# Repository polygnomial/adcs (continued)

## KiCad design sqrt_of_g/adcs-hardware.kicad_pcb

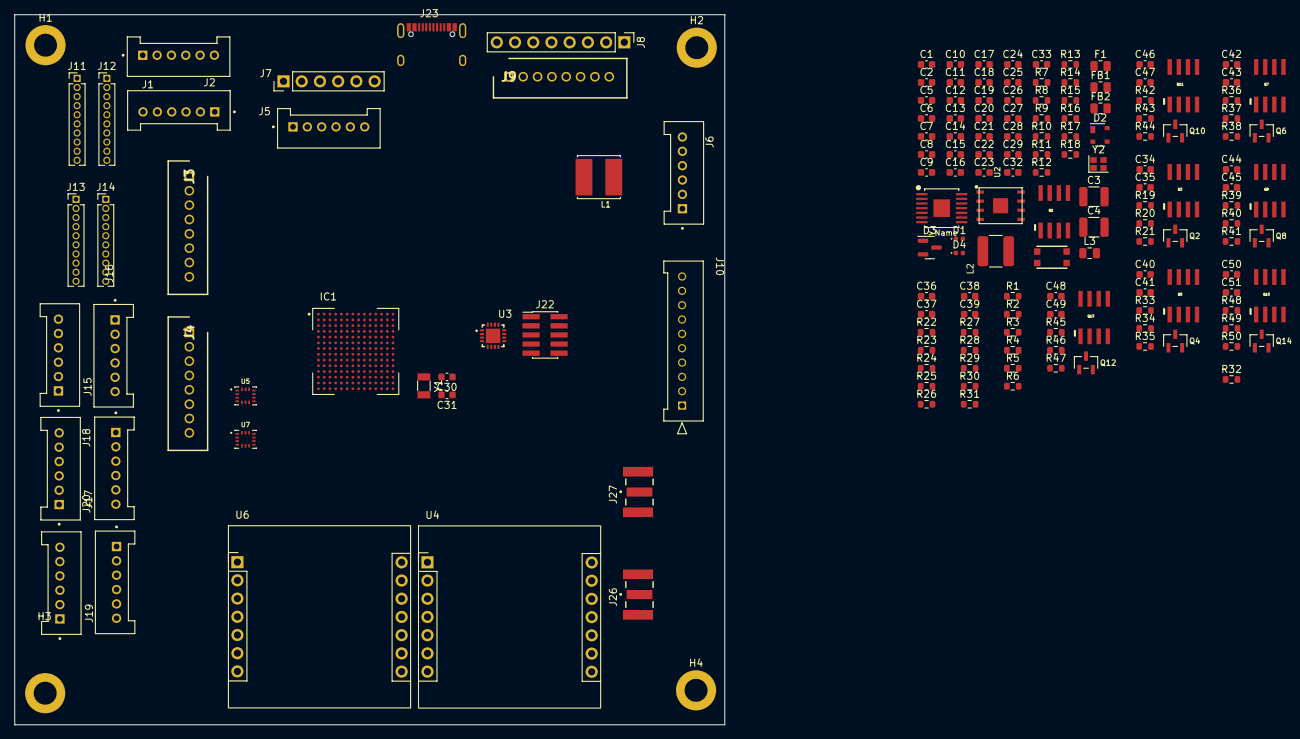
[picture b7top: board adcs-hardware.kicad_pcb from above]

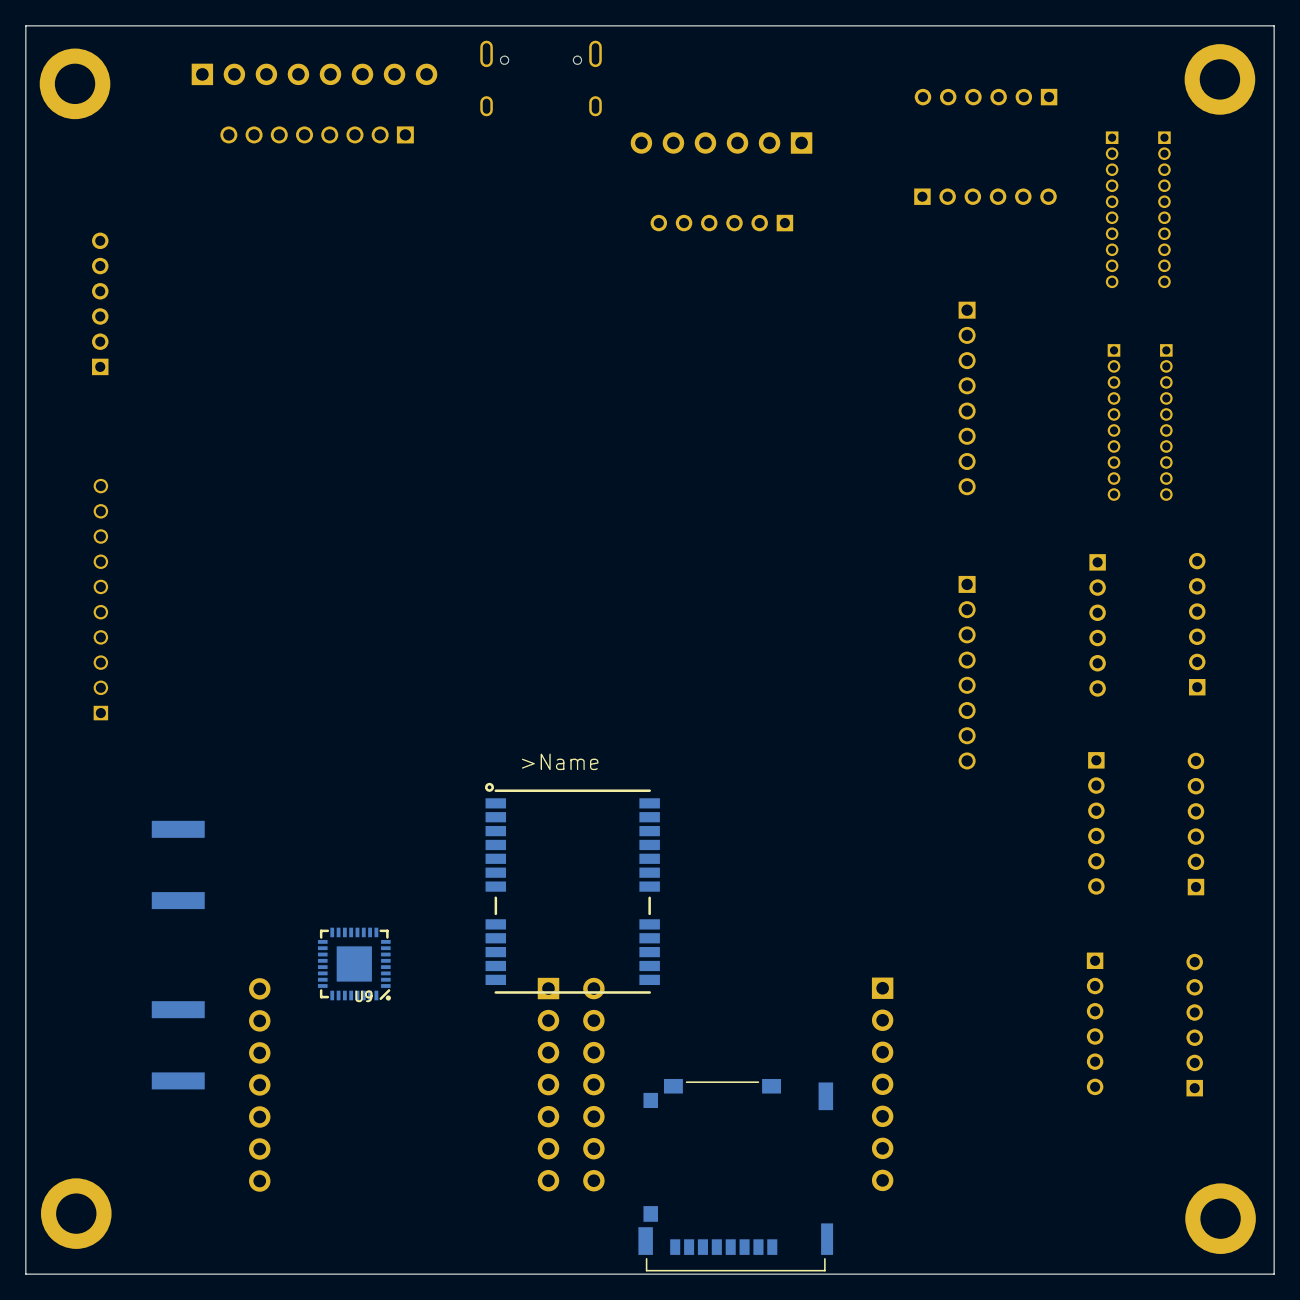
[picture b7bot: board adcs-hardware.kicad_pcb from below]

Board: 2 copper layers, 99.0 x 99.0 mm, 168 parts (3 on the bottom side), 189 nets, no tracks yet.

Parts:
C1, C2: 22uF; C_0603_1608Metric
C3, C4: 100uF; C_1210_3225Metric
C5, C9, C36, C37, C38, C39: 0.1uF; C_0603_1608Metric
C6, C7, C12, C16, C17, C23, C35, C41, C43, C45, C47, C49, C51: 4.7uF; C_0603_1608Metric
C8, C13, C15, C19, C20, C21, C22, C24, C25: 0.22uF; C_0603_1608Metric
C10: 3.3nF; C_0603_1608Metric
C11: 1uF; C_0603_1608Metric
C14, C27, C28, C29: 10uF; C_0603_1608Metric
C18, C34, C40, C42, C44, C46, C48, C50: 10nF; C_0603_1608Metric
C26: 2.2uF; C_0603_1608Metric
C30, C31, C32, C33: 10pF; C_0603_1608Metric
D1, D4: LED; LED_0402_1005Metric
D2: TVS Diode; SOT-143
D3: BAT54C; SOT-23
F1: Fuse; R_0805_2012Metric
FB1, FB2: FerriteBead; R_0805_2012Metric
H1, H2, H3, H4: MountingHole_Pad; MountingHole_3.2mm_M3_DIN965_Pad
IC1: MIMXRT1062DVJ6B; BGA196C80P14X14_1200X1200X152N
J1, J2, J5, J6, J15, J16, J17, J18, J19, J20: 353620650; MOLEX_35362-0650
J3, J4, J9: 353620850; SHDR8W50P0X200_1X8_1830X550X850P
J7: Conn_01x06; PinHeader_1x06_P2.54mm_Vertical
J8: Control Debug Header; PinHeader_1x08_P2.54mm_Vertical
J10: Thruster Connector; CON_353621050
J11, J12, J13, J14: Conn_01x10; PinHeader_1x10_P1.27mm_Vertical
J22: JTAG_SWD_10; PinHeader_2x05_P1.27mm_Vertical_SMD
J23: USB_C_pycubed; USB_C_Receptacle_XKB_U262-161N-4BVC11
J25: 503182-1852; MOLEX_503182-1852
J26, J27: SMA-J-P-H-ST-EM1; SAMTEC_SMA-J-P-H-ST-EM1
L1: 330uH; IND_SRN6045TA-331K
L2: 3.3uH; L_2141
L3: 4.7uH; C_0805_2012Metric
Q1, Q3, Q5, Q7, Q9, Q11, Q13, Q15: NDS8434
Q2, Q4, Q6, Q8, Q10, Q12, Q14: IRLML2803; SOT-23
R1, R2, R3, R4, R5, R6: 0; R_0603_1608Metric
R7: 73.2K; R_0603_1608Metric
R8, R17: 1k; R_0603_1608Metric
R9, R14: 100K; R_0603_1608Metric
R10: 22.1K; R_0603_1608Metric
R11, R12: 5.1k; R_0603_1608Metric
R13, R15, R18, R22, R23, R24, R25, R26, R27, R28, R29, R30, R31: 10k; R_0603_1608Metric
R16, R21, R35: 100k; R_0603_1608Metric
R19, R32, R33, R36, R39, R42, R45, R48: 10K; R_0603_1608Metric
R20, R34, R37, R40, R43, R46, R49: 4.7K; R_0603_1608Metric
R38, R41, R44, R47, R50: 3.3k; R_0603_1608Metric
SW1: KMR231NG LFS; BTN_KMR2_4.6X2.8
U1: TPS54226PWPR; PWP14_2P31X2P46-L
U2: MR25H40MDF; SON127P600X500X90-9N
U3: MKL02Z32VFG4; QFN50P300X300X65-17N
U4, U6: RM3100 Dev Board; RM3100
U5, U7: BMI270; XDCR_BMI270
U8: Orion B16; S1216_24PIN_PACKAGE
U9: EP2W+; QFN32-5X5MM
Y1: 32.768kHz; Crystal_SMD_3215-2Pin_3.2x1.5mm
Y2: 24.0mHz; Crystal_SMD_2016-4Pin_2.0x1.6mm

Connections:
3.3V: C9.1, D3.2, J25.4 (VDD), R13.2, R15.2, U2.8 (VDD)
+3V3: C1.2, C2.2, D1.2 (A), FB2.1, J5.1, J7.1, J15.4, J16.4, J17.4, J18.4, J19.4, J20.4, J22.1 (VTref), L2.2, Q7.1 (Source), Q7.2 (Source), Q7.3 (Source), Q9.1 (Source), Q9.2 (Source), Q9.3 (Source), Q11.1 (Source), Q11.2 (Source), Q11.3 (Source), Q13.1 (Source), Q13.2 (Source), Q13.3 (Source), Q15.1 (Source), Q15.2 (Source), Q15.3 (Source), R7.2, R9.2, R38.1, R41.1, R44.1, R47.1, R50.1, U1.1 (VO), U3.1 (VDD)
+5V: IC1.N6 (USB_OTG1_VBUS), IC1.P6 (USB_OTG2_VBUS), Q1.1 (Source), Q1.2 (Source), Q1.3 (Source)
+5VD: C6.2, D2.2 (K), F1.1, J5.6, J7.6, J23.A4 (VBUS), J23.A9 (VBUS)
/3V3_PD1: C48.1, C49.1, J2.1, J3.1, J3.5, Q13.5 (Drain), Q13.6 (Drain), Q13.7 (Drain), Q13.8 (Drain)
/3V3_PD2: C50.1, C51.1, J1.1, J4.1, J4.5, Q15.5 (Drain), Q15.6 (Drain), Q15.7 (Drain), Q15.8 (Drain)
/ADCS Power Enable/VBUS_IN: L1.2, Q5.1 (Source), Q5.2 (Source), Q5.3 (Source), R35.1
/Coil Power Enable/VBUS_OUT: C34.1, C35.1, J15.5, J16.5, J17.5, J18.5, J19.5, J20.5, Q3.5 (Drain), Q3.6 (Drain), Q3.7 (Drain), Q3.8 (Drain)
/EN_COILS: IC1.M14 (GPIO_AD_B0_00), R19.1, R20.1
/GPS/3V3_GPS: C46.1, C47.1, Q11.5 (Drain), Q11.6 (Drain), Q11.7 (Drain), Q11.8 (Drain), R32.2, U8.22 (V_BCKP), U8.23 (VCC)
/GPS/EN_GPS: IC1.E8 (GPIO_B0_02), R42.1, R43.1
/GPS/RF_IN: U8.11 (RF_IN), U9.4 (SUM_PORT)
/IMU1_and_MAG1/3V3_SENSORS: C36.1, C37.1, C42.1, C43.1, Q7.5 (Drain), Q7.6 (Drain), Q7.7 (Drain), Q7.8 (Drain), R24.2, R25.1, R26.1, U4.12 (DVDD), U4.13 (AVDD), U5.5 (VDDIO), U5.8 (VDD), U5.10 (OSCB)
/IMU1_and_MAG1/DRDY_MAG: IC1.C12 (GPIO_B1_06), U4.5 (DRDY)
/IMU1_and_MAG1/EN_SENSORS: IC1.E7 (GPIO_B0_01), R36.1, R37.1
/IMU2_and_MAG2/3V3_SENSORS: C38.1, C39.1, C44.1, C45.1, Q9.5 (Drain), Q9.6 (Drain), Q9.7 (Drain), Q9.8 (Drain), R29.2, R30.1, R31.1, U6.12 (DVDD), U6.13 (AVDD), U7.5 (VDDIO), U7.8 (VDD), U7.10 (OSCB)
/IMU2_and_MAG2/DRDY_MAG: IC1.D7 (GPIO_B0_00), U6.5 (DRDY)
/IMU2_and_MAG2/EN_SENSORS: IC1.A12 (GPIO_B1_08), R39.1, R40.1
/MCU/FLASH.CS: IC1.P5 (GPIO_SD_B1_11), U2.7 (~HOLD)
/MCU/FLASH.IO0: IC1.P3 (GPIO_SD_B1_08), U2.3 (~WP)
/MCU/FLASH.IO1: IC1.P4 (GPIO_SD_B1_10), U2.6 (SCK)
/MCU/FLASH.IO2: IC1.N4 (GPIO_SD_B1_09), U2.5 (SI)
/MCU/FLASH.IO3: IC1.L3 (GPIO_SD_B1_06), R15.1, U2.1 (~CS)
/MCU/FLASH.SCK: IC1.L4 (GPIO_SD_B1_07), U2.2 (SO)
/MCU/GPIO_AD_B0_01: IC1.H10 (GPIO_AD_B0_01), R5.1
/MCU/GPIO_AD_B0_03: IC1.G11 (GPIO_AD_B0_03), R6.1
/MCU/GPIO_AD_B0_12: IC1.K14 (GPIO_AD_B0_12), J3.3
/MCU/GPIO_AD_B0_13: IC1.L14 (GPIO_AD_B0_13), J3.4
/MCU/GPIO_AD_B0_14: IC1.H14 (GPIO_AD_B0_14), J3.7
/MCU/GPIO_AD_B0_15: IC1.L10 (GPIO_AD_B0_15), J3.8
/MCU/GPIO_AD_B1_00: IC1.J11 (GPIO_AD_B1_00), J2.3
/MCU/GPIO_AD_B1_01: IC1.K11 (GPIO_AD_B1_01), J2.4
/MCU/GPIO_AD_B1_04: IC1.L12 (GPIO_AD_B1_04), J2.5
/MCU/GPIO_AD_B1_05: IC1.K12 (GPIO_AD_B1_05), J2.6
/MCU/GPIO_AD_B1_06: IC1.J12 (GPIO_AD_B1_06), J4.3
/MCU/GPIO_AD_B1_07: IC1.K10 (GPIO_AD_B1_07), J4.4
/MCU/GPIO_AD_B1_08: IC1.H13 (GPIO_AD_B1_08), J4.7
/MCU/GPIO_AD_B1_09: IC1.M13 (GPIO_AD_B1_09), J4.8
/MCU/GPIO_AD_B1_10: IC1.L13 (GPIO_AD_B1_10), J1.3
/MCU/GPIO_AD_B1_11: IC1.J13 (GPIO_AD_B1_11), J1.4
/MCU/GPIO_AD_B1_12: IC1.H12 (GPIO_AD_B1_12), J1.5
/MCU/GPIO_AD_B1_13: IC1.H11 (GPIO_AD_B1_13), J1.6
/MCU/GPIO_AD_B1_14: IC1.G12 (GPIO_AD_B1_14), J14.5
/MCU/GPIO_AD_B1_15: IC1.J14 (GPIO_AD_B1_15), J14.6
/MCU/GPIO_B0_06: IC1.A8 (GPIO_B0_06), R48.1, R49.1
/MCU/GPIO_B0_07: IC1.A9 (GPIO_B0_07), R45.1, R46.1
/MCU/GPIO_B0_08: IC1.B9 (GPIO_B0_08), J13.1
/MCU/GPIO_B0_09: IC1.C9 (GPIO_B0_09), J13.2
/MCU/GPIO_B0_10: IC1.D9 (GPIO_B0_10), J13.3
/MCU/GPIO_B0_11: IC1.A10 (GPIO_B0_11), J13.4
/MCU/GPIO_B0_12: IC1.C10 (GPIO_B0_12), J13.5
/MCU/GPIO_B0_14: IC1.E10 (GPIO_B0_14), J13.6
/MCU/GPIO_B1_02: IC1.C11 (GPIO_B1_02), J12.1
/MCU/GPIO_B1_03: IC1.D11 (GPIO_B1_03), J12.2
/MCU/GPIO_B1_04: IC1.E12 (GPIO_B1_04), J12.3
/MCU/GPIO_B1_05: IC1.D12 (GPIO_B1_05), J12.4
/MCU/GPIO_B1_07: IC1.B12 (GPIO_B1_07), J12.5
/MCU/GPIO_B1_09: IC1.A13 (GPIO_B1_09), J12.6
/MCU/GPIO_B1_10: IC1.B13 (GPIO_B1_10), J11.1
/MCU/GPIO_B1_11: IC1.C13 (GPIO_B1_11), J11.2
/MCU/GPIO_B1_12: IC1.D13 (GPIO_B1_12), J11.3
/MCU/GPIO_B1_13: IC1.D14 (GPIO_B1_13), J11.4
/MCU/GPIO_B1_14: IC1.C14 (GPIO_B1_14), J11.5
/MCU/GPIO_B1_15: IC1.B14 (GPIO_B1_15), IC1.E11 (GPIO_B0_15), J11.6
/MCU/GPIO_EMC_00: IC1.D6 (GPIO_EMC_38), IC1.E3 (GPIO_EMC_00), J11.7
/MCU/GPIO_EMC_03: IC1.G4 (GPIO_EMC_03), J11.8
/MCU/GPIO_EMC_04: IC1.F2 (GPIO_EMC_04), J11.9
/MCU/GPIO_EMC_05: IC1.G5 (GPIO_EMC_05), R1.1
/MCU/GPIO_EMC_06: IC1.H5 (GPIO_EMC_06), R2.1
/MCU/GPIO_EMC_07: IC1.H4 (GPIO_EMC_07), J10.6
/MCU/GPIO_EMC_08: IC1.H3 (GPIO_EMC_08), J10.7
/MCU/GPIO_EMC_09: IC1.C2 (GPIO_EMC_09), J10.8
/MCU/GPIO_EMC_10: IC1.G1 (GPIO_EMC_10), J10.9
/MCU/GPIO_EMC_13: IC1.A6 (GPIO_EMC_13), J10.2
/MCU/GPIO_EMC_14: IC1.B6 (GPIO_EMC_14), J10.3
/MCU/GPIO_EMC_15: IC1.B1 (GPIO_EMC_15), J10.4
/MCU/GPIO_EMC_16: IC1.A5 (GPIO_EMC_16), J10.5
/MCU/GPIO_EMC_18: IC1.B2 (GPIO_EMC_18), J12.7
/MCU/GPIO_EMC_19: IC1.B4 (GPIO_EMC_19), J12.8
/MCU/GPIO_EMC_20: IC1.A3 (GPIO_EMC_20), J12.9
/MCU/GPIO_EMC_21: IC1.C1 (GPIO_EMC_21), J13.7
/MCU/GPIO_EMC_30: IC1.C6 (GPIO_EMC_30), J13.9
/MCU/GPIO_EMC_31: IC1.C5 (GPIO_EMC_31), J14.7
/MCU/GPIO_EMC_32: IC1.D5 (GPIO_EMC_32), J14.8
/MCU/GPIO_EMC_33: IC1.C4 (GPIO_EMC_33), J14.9
/MCU/GPIO_EMC_34: IC1.D4 (GPIO_EMC_34), R3.1
/MCU/GPIO_EMC_39: IC1.B7 (GPIO_EMC_39), R4.1
/MCU/GPIO_SD_B1_00: IC1.L5 (GPIO_SD_B1_00), J14.1
/MCU/GPIO_SD_B1_01: IC1.M5 (GPIO_SD_B1_01), J14.2
/MCU/GPIO_SD_B1_02: IC1.M3 (GPIO_SD_B1_02), J14.3
/MCU/GPIO_SD_B1_03: IC1.M4 (GPIO_SD_B1_03), J14.4
/MCU/JTAG.MUX.MOD: IC1.F13 (GPIO_AD_B0_08), U3.13 (PTB5)
/MCU/JTAG.MUX.TCK: IC1.F12 (GPIO_AD_B0_07), J22.4 (SWDCLK/TCK), U3.8 (PTB0)
/MCU/JTAG.MUX.TDI: IC1.F14 (GPIO_AD_B0_09), J22.8 (NC/TDI), U3.7 (PTA7)
/MCU/JTAG.MUX.TDO: IC1.G13 (GPIO_AD_B0_10), J22.6 (SWO/TDO), U3.6 (PTA6)
/MCU/JTAG.MUX.TMS: IC1.E14 (GPIO_AD_B0_06), J22.2 (SWDIO/TMS), U3.5 (PTA5)
/MCU/JTAG.MUX.TRSTB: IC1.G10 (GPIO_AD_B0_11), IC1.K3 (DCDC_PSWITCH), J22.10 (~RESET), R16.2, U3.3 (PTA3)
/MCU/ONOFF: IC1.M6 (ONOFF), J8.2, J9.2
/MCU/PMIC_STBY_REQ: IC1.L7 (PMIC_STBY_REQ), J8.4, J9.4, R18.2
/MCU/POR_B: IC1.M7 (POR_B), J8.5, J9.5, U3.9 (PTB1)
/MCU/SD.CLK: IC1.J3 (GPIO_SD_B0_01), J25.5 (CLK)
/MCU/SD.CMD: IC1.J4 (GPIO_SD_B0_00), J25.3 (CMD)
/MCU/SD.DAT0: IC1.J1 (GPIO_SD_B0_02), J25.7 (DAT0)
/MCU/SD.DAT1: IC1.K1 (GPIO_SD_B0_03), J25.8 (DAT1)
/MCU/SD.DAT2: IC1.H2 (GPIO_SD_B0_04), J25.1 (DATA2)
/MCU/SD.DAT3: IC1.J2 (GPIO_SD_B0_05), J25.2 (CD/DAT3), R13.1
/MCU/USB1_CC1: J23.A5 (CC1), R11.2
/MCU/USB1_CC2: J23.B5 (CC2), R12.2
/MCU/USB1_D+: D2.4 (K), IC1.L8 (USB_OTG1_DP), J23.A6 (D+), J23.B6 (D+)
/MCU/USB1_D-: D2.3 (K), IC1.M8 (USB_OTG1_DN), J23.A7 (D-), J23.B7 (D-)
/MCU/WAKEUP: IC1.L6 (WAKEUP), J8.3, J9.3
/RX_FROM_GPS: IC1.B11 (GPIO_B1_01), U8.20 (TXD)
/RX_FROM_PYCUBED: IC1.L11 (GPIO_AD_B1_02), J8.6, J9.6
/SCL2: IC1.C8 (GPIO_B0_04), J15.1, J18.1, R25.2, U4.1 (SCK/SCL), U5.13 (SCX)
/SCL4: IC1.H1 (GPIO_EMC_12), J16.1, J17.1, J19.1, J20.1, R30.2, U6.1 (SCK/SCL), U7.13 (SCX)
/SDA2: IC1.B8 (GPIO_B0_05), J15.2, J18.2, R26.2, U4.3 (SI/SDA), U5.14 (SDX)
/SDA4: IC1.G3 (GPIO_EMC_11), J16.2, J17.2, J19.2, J20.2, R31.2, U6.3 (SI/SDA), U7.14 (SDX)
/TX_TO_GPS: IC1.A11 (GPIO_B1_00), U8.21 (RXD)
/TX_TO_PYCUBED: IC1.M12 (GPIO_AD_B1_03), J8.7, J9.7
/VBATT: C3.1, C4.1, C40.1, C41.1, J5.5, J7.5, Q3.1 (Source), Q3.2 (Source), Q3.3 (Source), Q5.5 (Drain), Q5.6 (Drain), Q5.7 (Drain), Q5.8 (Drain), R21.1, U1.13 (VIN), U1.14 (VCC)
/VBATT_IN: J6.1, J6.3, J6.5, L1.1
GND: C1.1, C2.1, C3.2, C4.2, C7.2, C8.2, C9.2, C10.2, C11.2, C12.2, C13.2, C14.2, C15.2, C16.2, C17.2, C18.2, C19.2, C20.2, C21.2, C22.2, C23.2, C24.2, C25.2, C26.2, C27.2, C28.2, C29.2, C30.2, C31.2, C32.2, C33.2, C36.2, C37.2, C38.2, C39.2, D4.1 (K), H1.1, H2.1, H3.1, H4.1, IC1.A1 (VSS_1), IC1.A14 (VSS_2), IC1.B5 (VSS_3), IC1.B10 (VSS_4), IC1.E2 (VSS_5), IC1.E13 (VSS_6), IC1.G7 (VSS_7), IC1.G8 (VSS_8), IC1.G14 (GPIO_AD_B0_05), IC1.H7 (VSS_9), IC1.H8 (VSS_10), IC1.J7 (VSS_11), IC1.J8 (VSS_12), IC1.K2 (VSS_13), IC1.K6 (TEST_MODE), IC1.K9 (NGND_KEL0), IC1.K13 (VSS_14), IC1.L9 (VSS_15), IC1.N1 (DCDC_GND_1), IC1.N2 (DCDC_GND_2), IC1.N5 (VSS_16), IC1.N8 (VSS_17), IC1.P1 (VSS_18), IC1.P14 (VSS_19), J1.2, J2.2, J3.2, J3.6, J4.2, J4.6, J5.2, J5.4, J6.2, J6.4, J6.6, J7.2, J7.4, J8.1, J9.1, J10.1, J10.10, J11.10, J12.10, J13.10, J14.10, J15.3, J16.3, J17.3, J18.3, J19.3, J20.3, J22.3 (GND), J22.5 (GND), J22.9 (GNDDetect), J25.6 (VSS), J25.P1 (SHIELD), J25.P2 (SHIELD), J25.P3 (SHIELD), J25.P4 (SHIELD), J25.P5 (SHIELD), J26.2_1, J27.2_1, Q1.4 (Gate), Q2.2 (S), Q4.2 (S), Q6.2 (S), Q8.2 (S), Q10.2 (S), Q12.2 (S), Q14.2 (S), R10.1, R16.1, R18.1, R19.2, R22.1, R23.1, R27.1, R28.1, R33.1, R33.2, R34.1, R36.2, R39.2, R42.2, R45.2, R48.2, SW1.B (S), SW1.B' (S1), U1.5 (GND), U1.8 (PGND1), U1.9 (PGND2), U1.15 (EPAD), U2.4 (VSS), U2.9 (EP), U3.2 (VSS), U3.17 (EPAD), U4.7 (AVSS), U4.14 (DVSS), U5.1 (SDO), U5.6 (GNDIO), U5.7 (GND), U6.7 (AVSS), U6.14 (DVSS), U7.1 (SDO), U7.6 (GNDIO), U7.7 (GND), U8.10 (GND@10), U8.12 (GND@12), U8.13 (GND@13), U8.24 (GND@24), U9.1 (GND), U9.2 (GND), U9.3 (GND), U9.5 (GND), U9.6 (GND), U9.7 (GND), U9.8 (GND), U9.9 (GND), U9.10 (GND), U9.11 (GND), U9.12 (GND), U9.13 (GND), U9.14 (GND), U9.16 (GND), U9.17 (GND), U9.18 (GND), U9.19 (GND), U9.20 (GND), U9.21 (GND), U9.22 (GND), U9.23 (GND), U9.24 (GND), U9.25 (GND), U9.27 (GND), U9.28 (GND), U9.29 (GND), U9.30 (GND), U9.31 (GND), U9.32 (GND), U9.EP (GND)
GNDREF: C6.1, D2.1 (A), J5.3, J7.3, J23.A1 (GND), J23.A12 (GND), J23.S1 (SHIELD), R11.1, R12.1
unnamed: C34.2, C35.2
unnamed: C40.2, C41.2
unnamed: C42.2, C43.2
unnamed: C44.2, C45.2
unnamed: C46.2, C47.2
unnamed: C48.2, C49.2
unnamed: C50.2, C51.2
unnamed: D1.1 (K), R8.2
unnamed: D4.2 (A), R17.2
unnamed: F1.2, FB1.1
unnamed: FB1.2, Q1.5 (Drain), Q1.6 (Drain), Q1.7 (Drain), Q1.8 (Drain)
unnamed: C17.1, C24.1, C28.1, FB2.2, IC1.L1 (DCDC_IN_1), IC1.L2 (DCDC_IN_2)
unnamed: IC1.M1 (DCDC_LP_1), IC1.M2 (DCDC_LP_2), L3.2
unnamed: C18.1, C23.1, C25.1, C29.1, IC1.F6 (VDD_SOC_IN_1), IC1.F7 (VDD_SOC_IN_2), IC1.F8 (VDD_SOC_IN_3), IC1.F9 (VDD_SOC_IN_4), IC1.G6 (VDD_SOC_IN_5), IC1.G9 (VDD_SOC_IN_6), IC1.H6 (VDD_SOC_IN_7), IC1.H9 (VDD_SOC_IN_8), IC1.J5 (DCDC_SENSE), IC1.J9 (VDD_SOC_IN_9), L3.1
unnamed: C15.1, C16.1, C21.1, C22.1, C26.1, C27.1, IC1.E6 (NVCC_EMC_1), IC1.E9 (NVCC_GPIO_1), IC1.F4 (GPIO_EMC_02), IC1.F5 (NVCC_EMC_2), IC1.F10 (NVCC_GPIO_2), IC1.J6 (NVCC_SD0), IC1.J10 (NVCC_GPIO_3), IC1.K4 (DCDC__IN_Q), IC1.K5 (NVCC_SD1), IC1.N14 (VDDA_ADC_3P3), IC1.P12 (VDD_HIGH_IN)
unnamed: IC1.F11 (GPIO_AD_B0_04), U3.4 (PTA4)
unnamed: IC1.D8 (GPIO_B0_03), R17.1
unnamed: IC1.D10 (GPIO_B0_13), U3.12 (PTB4)
unnamed: IC1.F3 (GPIO_EMC_01), U3.15 (PTA1)
unnamed: C12.1, C13.1, IC1.P10 (NVCC_PLL)
unnamed: IC1.K7 (PMIC_ON_REQ), R9.1, U1.7 (EN)
unnamed: C33.1, IC1.N9 (RTC_XTALI), Y2.1
unnamed: C32.1, IC1.P9 (RTC_XTALO), Y2.2
unnamed: C7.1, C8.1, IC1.P8 (VDD_HIGH_CAP)
unnamed: C19.1, IC1.M10 (VDD_SNVS_CAP)
unnamed: D3.3, IC1.M9 (VDD_SNVS_IN)
unnamed: C14.1, C20.1, D3.1, IC1.K8 (VDD_USB_CAP)
unnamed: C31.1, IC1.P11 (XTALI), Y1.1
unnamed: C30.1, IC1.N11 (XTALO), Y1.2
unnamed: J15.6, R1.2
unnamed: J16.6, R2.2
unnamed: J17.6, R3.2
unnamed: J18.6, R4.2
unnamed: J19.6, R5.2
unnamed: J20.6, R6.2
unnamed: Q2.3 (D), Q3.4 (Gate), R21.2
unnamed: Q2.1 (G), R20.2
unnamed: Q4.3 (D), Q5.4 (Gate), R35.2
unnamed: Q4.1 (G), R34.2
unnamed: Q6.3 (D), Q7.4 (Gate), R38.2
unnamed: Q6.1 (G), R37.2
unnamed: Q8.3 (D), Q9.4 (Gate), R41.2
unnamed: Q8.1 (G), R40.2
unnamed: Q10.3 (D), Q11.4 (Gate), R44.2
unnamed: Q10.1 (G), R43.2
unnamed: Q12.3 (D), Q13.4 (Gate), R47.2
unnamed: Q12.1 (G), R46.2
unnamed: Q14.3 (D), Q15.4 (Gate), R50.2
unnamed: Q14.1 (G), R49.2
unnamed: SW1.A, SW1.A' (P1), U3.10 (PTB2)
unnamed: R14.1, U1.6 (PG)
unnamed: C10.1, U1.4 (SS)
unnamed: C5.1, L2.1, U1.10 (SW1), U1.11 (SW2)
unnamed: C5.2, U1.12 (VBST)
unnamed: R7.1, R10.2, U1.2 (VFB)
unnamed: C11.1, R14.2, U1.3 (VREG5)
unnamed: R8.1, U3.11 (PTB3)
unnamed: R24.1, U4.10 (I2CEN)
unnamed: R22.2, U4.2 (SO/ADDR1)
unnamed: R23.2, U4.4 (SSN/ADDR0)
unnamed: R29.1, U6.10 (I2CEN)
unnamed: R27.2, U6.2 (SO/ADDR1)
unnamed: R28.2, U6.4 (SSN/ADDR0)
unnamed: R32.1, U8.8 (RSTN)
unnamed: J27.1, U9.15 (PORT1)
unnamed: J26.1, U9.26 (PORT2)

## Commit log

2023-10-06 add gitignore
2023-10-06 add rough schematic
2023-10-10 schematic update
2023-10-10 add datasheet for teensy
2023-10-10 update schematic
2023-10-19 organize
2023-10-20 ready for review
2023-10-20 add datasheets
2023-10-20 beginning light sensing calcs
2023-10-20 add gnd pins
2023-10-20 pete feedback
2023-10-21 rename datasheets
2023-10-21 save
2023-10-25 add pyramidal breakout board
2023-10-25 move mainboard to subdirectory
2023-10-25 add math and decals
2023-10-26 ordered sfh2430 breakout rev 0.1
2023-10-30 more schematic work... I was supposed to finish this a long time ago
2023-10-30 add inertia calcs
2023-10-30 clean up msft gitignore
2023-10-30 add some symbols!
2023-11-01 ready for 2nd round of reviews
2023-11-01 add notes
2023-11-07 add mainboard footprints
2023-11-07 add footprints to adcs lib
2023-11-07 add models
2023-11-07 update ibom for photodiode breakout
2023-11-07 add C++ gitignore
2023-11-07 update board
2023-11-07 update pin map
2023-11-07 we have some software!
2023-11-07 move code up a folder
2023-11-07 fix RM3100 read bug and remove debug printing
2023-11-23 add pyramid stl
2023-11-24 sfh2400 v2 (flex PCB)
2023-11-25 add rusty flight target
2024-01-01 update libraries
2024-01-01 add kibot workflow
2024-01-01 rename kibot run
2024-01-01 oopsies
2024-01-01 update gps schematic
2024-01-01 update kibot version
2024-01-01 update main board
2024-01-01 remove prod folder
2024-01-01 add gps code
2024-01-01 add teensy 4.1 pinout
2024-01-01 add 3d models
2024-01-01 add rad testing reports for rm3100
2024-01-01 update pin map, add RT1176 pin map
2024-01-01 add rt1170 datasheet and mag sensor layout guidelines
2024-01-01 add note to tim review
2024-01-01 add FDSOI rad ref, mag sensor calibration references
2024-01-01 semi-working rust code
2024-01-01 add photodiode pics to the subdir
2024-01-01 try new kibot setup
2024-01-01 update run
2024-01-08 rust driver for RM3100, re-organize
2024-01-08 update gitignore
2024-01-08 don't ground enable pin
2024-01-08 migrate cpp code
2024-01-16 ffc/fpc pyramid
2024-01-16 add datasheet
2024-01-17 add submodules
2024-01-17 small
2024-01-17 add deps
2024-01-17 restore from backup
2024-01-17 bump libgeomag
2024-01-17 add triad
2024-01-17 optimize deps
2024-01-17 cargo fix
2024-01-18 switch to quaternion
2024-01-18 update libs
2024-02-02 fix photodiode pair
2024-02-02 add lots of datasheets
2024-02-02 update coil control
2024-02-02 add parts to library
2024-02-02 cpu board in progress
2024-02-05 b2b done, erc no errors
2024-02-05 work on sun pyramid
2024-02-05 update symbol library
2024-02-06 fix most footprints
2024-02-06 JLC parts list complete
2024-02-06 add boot switches and fix footprints
2024-02-06 std size for schematic labels, rm passive lbls
2024-02-06 add todos and clean up labels
2024-02-08 clean up board2board connector and organize TODOs
2024-02-09 add radiation test papers
2024-02-09 add ECC and low power mode application notes
2024-02-20 route most of power distribution
2024-02-20 clean up pwr slightly
2024-02-21 floorplan complete
2024-02-21 add models and power diagram
2024-02-25 continue work on fanout
2024-02-25 grounded
2024-02-26 add load switch
2024-02-26 move level shifter to top
2024-02-26 pre-autorouter
2024-02-27 99 bottles of DRC error on the wall, 99 bottles of DRC error...
2024-02-27 clean up silkscreen
2024-02-28 soldermander 1.0 ready for review
2024-02-28 PCBranch ready for review
2024-02-28 rename to Soldermander
2024-02-28 move boards to hardware/
2024-02-28 add readme!
2024-02-29 update 3.3uH inductor
2024-07-26 pre-autorouter part 2
2024-07-26 --amend
2024-07-26 1.0.1
2024-08-06 ads board 1.0.1
2024-08-06 PrintedCoralBoard
2024-08-06 PCB routing and silkscreen
2024-08-06 add pics
2024-08-06 fix landing pattern
2024-08-08 add PiCoral 1.0.0
2024-08-08 update names
